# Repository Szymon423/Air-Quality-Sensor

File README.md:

<div align="center">

# Air Quality Sensor

**A compact, open-hardware indoor air quality monitor built around the ESP32-S3.**
Measures CO₂, temperature, humidity and pressure, and shows the room's air quality on a ring of RGB LEDs.

</div>

---

## Features

- **True CO₂ measurement.** Sensirion **SCD41** photoacoustic NDIR sensor, not an estimated eCO₂ value.
- **Temperature & humidity.** Sensirion **SHT4x**, placed on a thermally isolated PCB island (milled slot) to keep it away from heat from the MCU and regulator.
- **Barometric pressure.** Goertek **SPA06-003**.
- **Wi-Fi + Bluetooth LE.** **ESP32-S3-WROOM-1U** with an external antenna connector (U.FL).
- **16× WS2812 LED ring** on the bottom side, shining through a translucent diffuser. The 5 V data line goes through a 74AHCT1G125 level shifter.
- **USB-C power** with ESD protection (USBLC6-2) and fuses, plus a TPS54302 buck regulator for the 3.3 V rail.
- **Expansion port.** JST-PH 4-pin connector with 3.3 V, GND and two free GPIOs.
- **Debug UART header** and test points on every important net.
- **Round Ø70 mm PCB** in a 3D-printable enclosure with angled ventilation slots.

## Gallery

<table>
  <tr>
    <td align="center"><br><sub>USB-C side</sub></td>
    <td align="center"><br><sub>Bottom with LED diffuser</sub></td>
  </tr>
</table>

### PCB

<table>
  <tr>
    <td align="center" width="50%"><br><sub>Top side</sub></td>
    <td align="center" width="50%"><br><sub>Bottom side – LED ring</sub></td>
  </tr>
</table>

📄 **[Schematic (PDF)](docs/schematic.pdf)**

## Hardware overview

| Block | Part | Notes |
|---|---|---|
| MCU | ESP32-S3-WROOM-1U | Wi-Fi 4 / BLE 5, external antenna |
| CO₂ | Sensirion SCD41 | 400–5000 ppm, I²C |
| Temperature / RH | Sensirion SHT4x | I²C, thermally isolated |
| Pressure | Goertek SPA06-003 | I²C |
| Indicator | 16× WS2812C-2020 | Driven through 74AHCT1G125 level shifter |
| Power | USB-C → TPS54302 buck → 3.3 V | USBLC6-2 ESD protection, PTC fuses |
| PCB | Ø70 mm, round | Designed for JLCPCB assembly (LCSC part numbers in BOM) |

```
 USB-C ──► ESD + fuse ──► TPS54302 ──► 3.3 V ─┬─► ESP32-S3 ──I²C──┬─► SCD41  (CO₂)
   │                                          │       │           ├─► SHT4x  (T / RH)
   └──────────── 5 V ─────────────────────────┼───────┼──────┐    └─► SPA06  (pressure)
                                              │       │      ▼
                                              │       └──► 74AHCT1G125 ──► 16× WS2812 ring
                                              └─► JST-PH expansion (2× GPIO)
```

## Repository structure

```
.
├── 01_Hardware/
│   ├── 02_KiCad/
│   │   ├── air-quality-sensor/    # KiCad project (schematic + PCB)
│   │   │   └── production/        # Gerbers, BOM, pick & place (JLCPCB)
│   │   └── lib/                   # Custom symbols, footprints, 3D models
│   └── 03_3D_Model/
│       ├── 3D-Printing/           # Enclosure STL / 3MF files
│       └── test.blend             # Blender scene used for the renders
├── 02_Software/                   # Firmware (coming soon)
└── docs/                          # Images and schematic PDF for this README
```

## Roadmap

- [x] Schematic
- [x] PCB layout v0.1 (Ø70 mm)
- [x] Enclosure design & renders
- [ ] Order and assemble the first prototype
- [ ] Hardware bring-up & validation
- [ ] Firmware: sensor readout, LED air-quality indication
- [ ] Home Assistant integration (ESPHome / MQTT)
- [ ] Hardware v1.0 release

## Building one

> [!WARNING]
> This project is **work in progress**. Hardware v0.1 has not been manufactured and tested yet, so order boards at your own risk.

1. Open `01_Hardware/02_KiCad/air-quality-sensor/air-quality-sensor.kicad_pro` in **KiCad 10**.
2. The fabrication files (Gerbers, BOM, CPL) for JLCPCB are in `production/`.
3. Print the enclosure from `01_Hardware/03_3D_Model/3D-Printing/`.

## License

**Hardware** (schematics, PCB, enclosure, renders): [**CC BY-NC-SA 4.0**](LICENSE).
You may build, study and modify this design for **non-commercial** purposes, as long as you credit the author and share your changes under the same license.
**Selling boards, kits or devices based on this design is not allowed** without the author's written permission.

**Firmware** (`02_Software/`): [**GPL-3.0**](02_Software/LICENSE).

For commercial licensing, please get in touch.

---

<div align="center">
<sub>Designed by <b>Szymon Wąchała</b> · 2026</sub>
</div>

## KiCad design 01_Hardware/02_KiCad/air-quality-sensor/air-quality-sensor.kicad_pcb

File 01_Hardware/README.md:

# Hardware | Air Quality Sensor

| Folder | Contents |
|---|---|
| [`02_KiCad/air-quality-sensor`](02_KiCad/air-quality-sensor) | KiCad 10 project: schematic sheets (`mcu`, `sensors`, `led-ring`, `power-section`) and PCB |
| [`02_KiCad/air-quality-sensor/production`](02_KiCad/air-quality-sensor/production) | JLCPCB fabrication output: Gerbers, BOM, pick & place |
| [`02_KiCad/lib`](02_KiCad/lib) | Project-specific libraries and 3D models |
| [`03_3D_Model/3D-Printing`](03_3D_Model/3D-Printing) | Enclosure parts for 3D printing |

A PDF of the schematic is in [`docs/schematic.pdf`](../docs/schematic.pdf).

Licensed under [CC BY-NC-SA 4.0](../LICENSE).

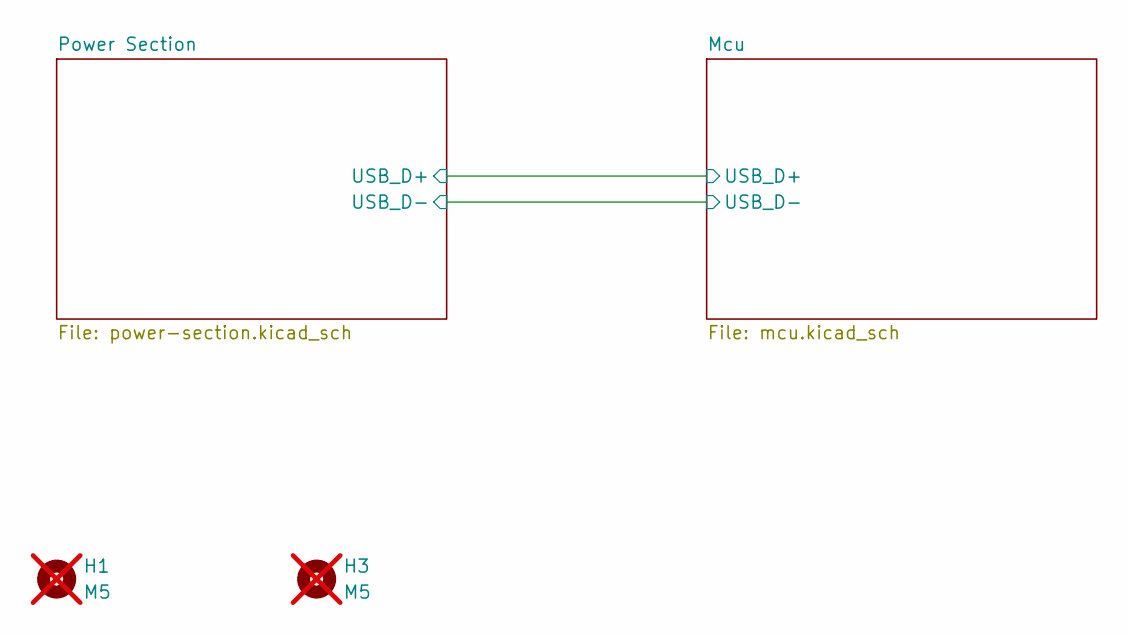
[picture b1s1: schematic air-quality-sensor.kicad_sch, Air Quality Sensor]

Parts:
H1, H3: M5; MountingHole_5mm; not fitted

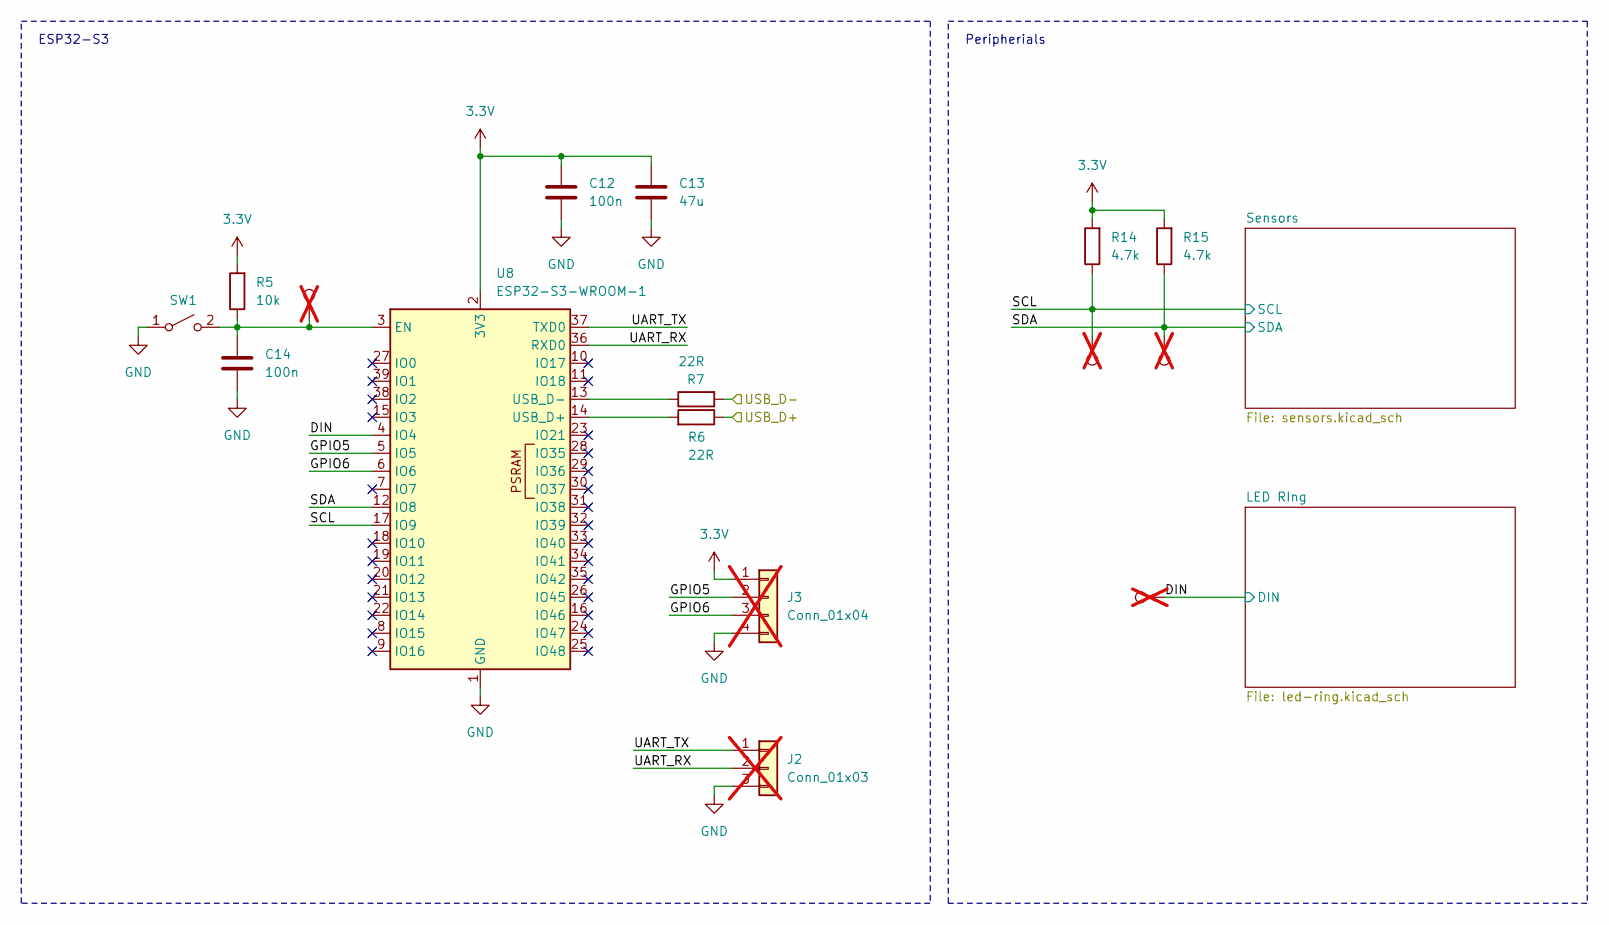
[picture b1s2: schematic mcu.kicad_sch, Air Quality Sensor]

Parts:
C12, C14: 100n; C_0603_1608Metric; LCSC C14663
C13: 47u; C_1206_3216Metric; LCSC C96123
J2: Conn_01x03; PinHeader_1x03_P2.54mm_Vertical; not fitted
J3: Conn_01x04; JST_PH_B4B-PH-K_1x04_P2.00mm_Vertical; not fitted
R5: 10k; R_0603_1608Metric; LCSC C22369937
R6, R7: 22R; R_0603_1608Metric; LCSC C23345
R14, R15: 4.7k; R_0603_1608Metric; LCSC C23162
SW1: SW_SPST; SW_Push_1P1T_NO_CK_KMR2; LCSC C72443
TP4, TP5, TP6, TP9: 3.3V; TestPoint_Pad_D1.0mm; not fitted
U8: ESP32-S3-WROOM-1; ESP32-S3-WROOM-1U; LCSC C2980297

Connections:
3.3V: C12.2, C13.1, J3.1, R5.2, R14.2, R15.2, U8.2 (3V3); also elsewhere on the board
/Mcu/DIN: TP9.1 (1_1), U8.4 (IO4); also elsewhere on the board
/Mcu/GPIO5: J3.2, U8.5 (IO5)
/Mcu/GPIO6: J3.3, U8.6 (IO6)
/Mcu/SCL: R14.1, TP5.1 (1_1), U8.17 (IO9); also elsewhere on the board
/Mcu/SDA: R15.1, TP4.1 (1_1), U8.12 (IO8); also elsewhere on the board
/Mcu/UART_RX: J2.2, U8.36 (RXD0)
/Mcu/UART_TX: J2.1, U8.37 (TXD0)
/Mcu/USB_D+: R6.1; also elsewhere on the board
/Mcu/USB_D-: R7.2; also elsewhere on the board
GND: C12.1, C13.2, C14.1, J2.3, J3.4, SW1.1 (A), U8.1 (GND), U8.40 (GND), U8.41 (GND); also elsewhere on the board
unnamed: C14.2, R5.1, SW1.2 (B), TP6.1 (1_1), U8.3 (EN)
unnamed: R6.2, U8.14 (USB_D+)
unnamed: R7.1, U8.13 (USB_D-)

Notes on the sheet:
ESP32-S3
Peripherials

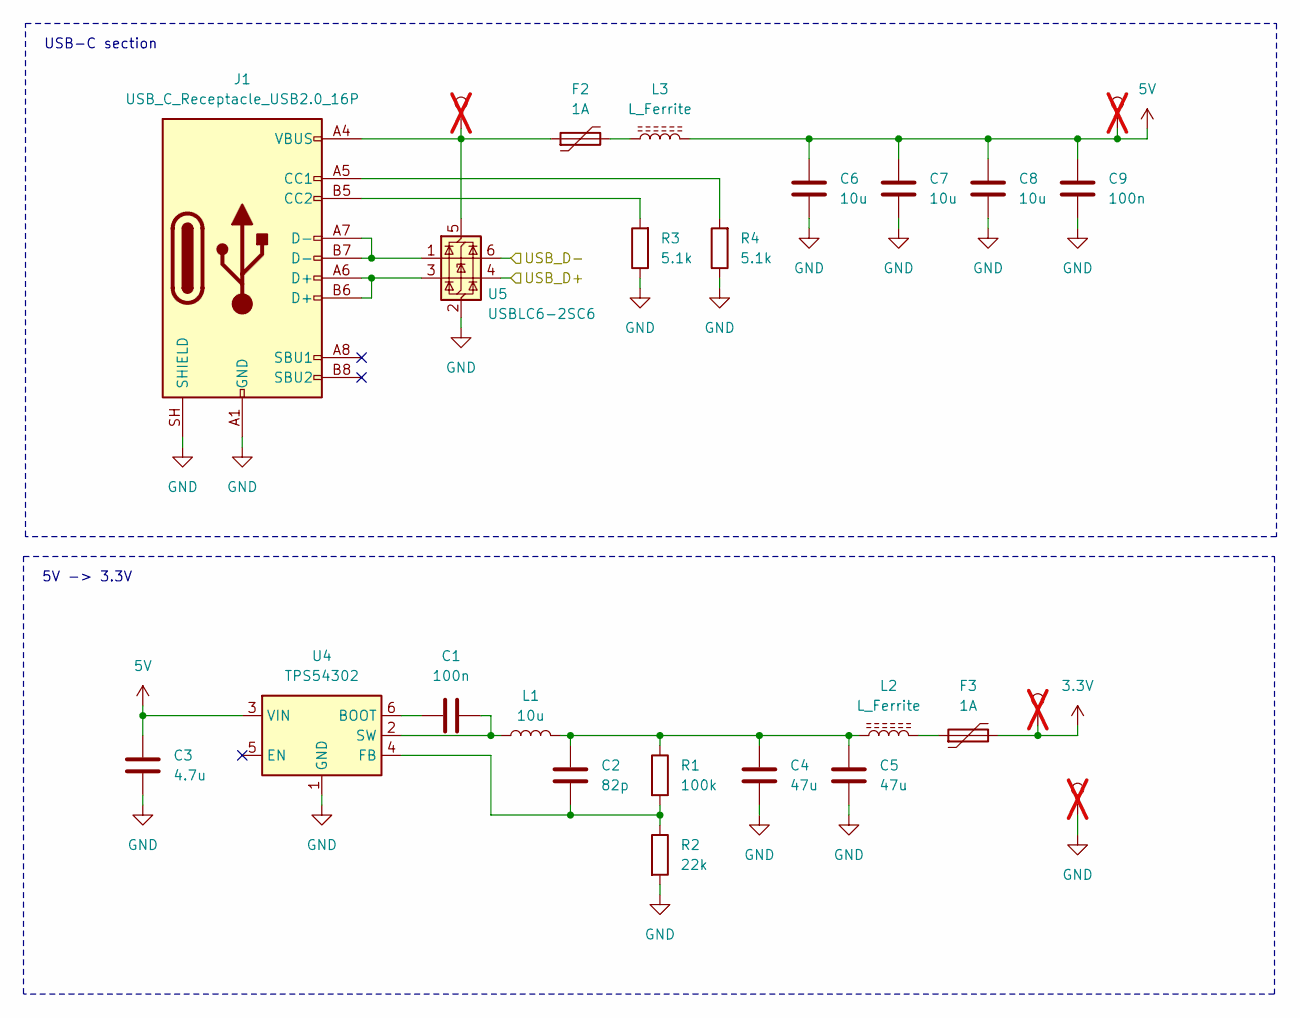
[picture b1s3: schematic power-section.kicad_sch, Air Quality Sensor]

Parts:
C1, C9: 100n; C_0603_1608Metric; LCSC C14663
C2: 82p; C_0603_1608Metric; LCSC C1683
C3: 4.7u; C_0805_2012Metric; LCSC C1779
C4, C5: 47u; C_1206_3216Metric; LCSC C96123
C6, C7, C8: 10u; C_1206_3216Metric; LCSC C13585
F2, F3: 1A; R_1206_3216Metric; LCSC C561579
J1: USB_C_Receptacle_USB2.0_16P; USB_C_Receptacle_GCT_USB4105-xx-A_16P_TopMnt_Horizontal; LCSC C3020560
L1: 10u; L_APV_ANR6045; LCSC C354632
L2, L3: L_Ferrite; L_0603_1608Metric; LCSC C14709
R1: 100k; R_0603_1608Metric; LCSC C25803
R2: 22k; R_0603_1608Metric; LCSC C31850
R3, R4: 5.1k; R_0603_1608Metric; LCSC C23186
TP1, TP2, TP3, TP10: 3.3V; TestPoint_Pad_D1.0mm; not fitted
U4: TPS54302; SOT-23-6; LCSC C129370
U5: USBLC6-2SC6; SOT-23-6; LCSC C558442

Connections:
3.3V: F3.2, TP1.1 (1_1); also elsewhere on the board
5V: C3.1, C6.1, C7.1, C8.1, C9.2, L3.2, TP2.1 (1_1), U4.3 (VIN); also elsewhere on the board
/Mcu/USB_D+: U5.4 (I/O2); also elsewhere on the board
/Mcu/USB_D-: U5.6 (I/O1); also elsewhere on the board
GND: C3.2, C4.2, C5.2, C6.2, C7.2, C8.2, C9.1, J1.A1 (GND), J1.A12 (GND), J1.B1 (GND), J1.B12 (GND), J1.SH (SHIELD), R2.2, R3.1, R4.1, TP10.1 (1_1), U4.1 (GND), U5.2 (GND); also elsewhere on the board
unnamed: C2.2, C4.1, C5.1, L1.2, L2.1, R1.1
unnamed: F2.2, L3.1
unnamed: F3.1, L2.2
unnamed: J1.A5 (CC1), R4.2
unnamed: J1.B5 (CC2), R3.2
unnamed: J1.A6 (D+), J1.B6 (D+), U5.3 (I/O2)
unnamed: J1.A7 (D-), J1.B7 (D-), U5.1 (I/O1)
unnamed: C1.1, U4.6 (BOOT)
unnamed: C2.1, R1.2, R2.1, U4.4 (FB)
unnamed: C1.2, L1.1, U4.2 (SW)
unnamed: F2.1, J1.A4 (VBUS), J1.A9 (VBUS), J1.B4 (VBUS), J1.B9 (VBUS), TP3.1 (1_1), U5.5 (VBUS)

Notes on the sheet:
5V -> 3.3V
USB-C section

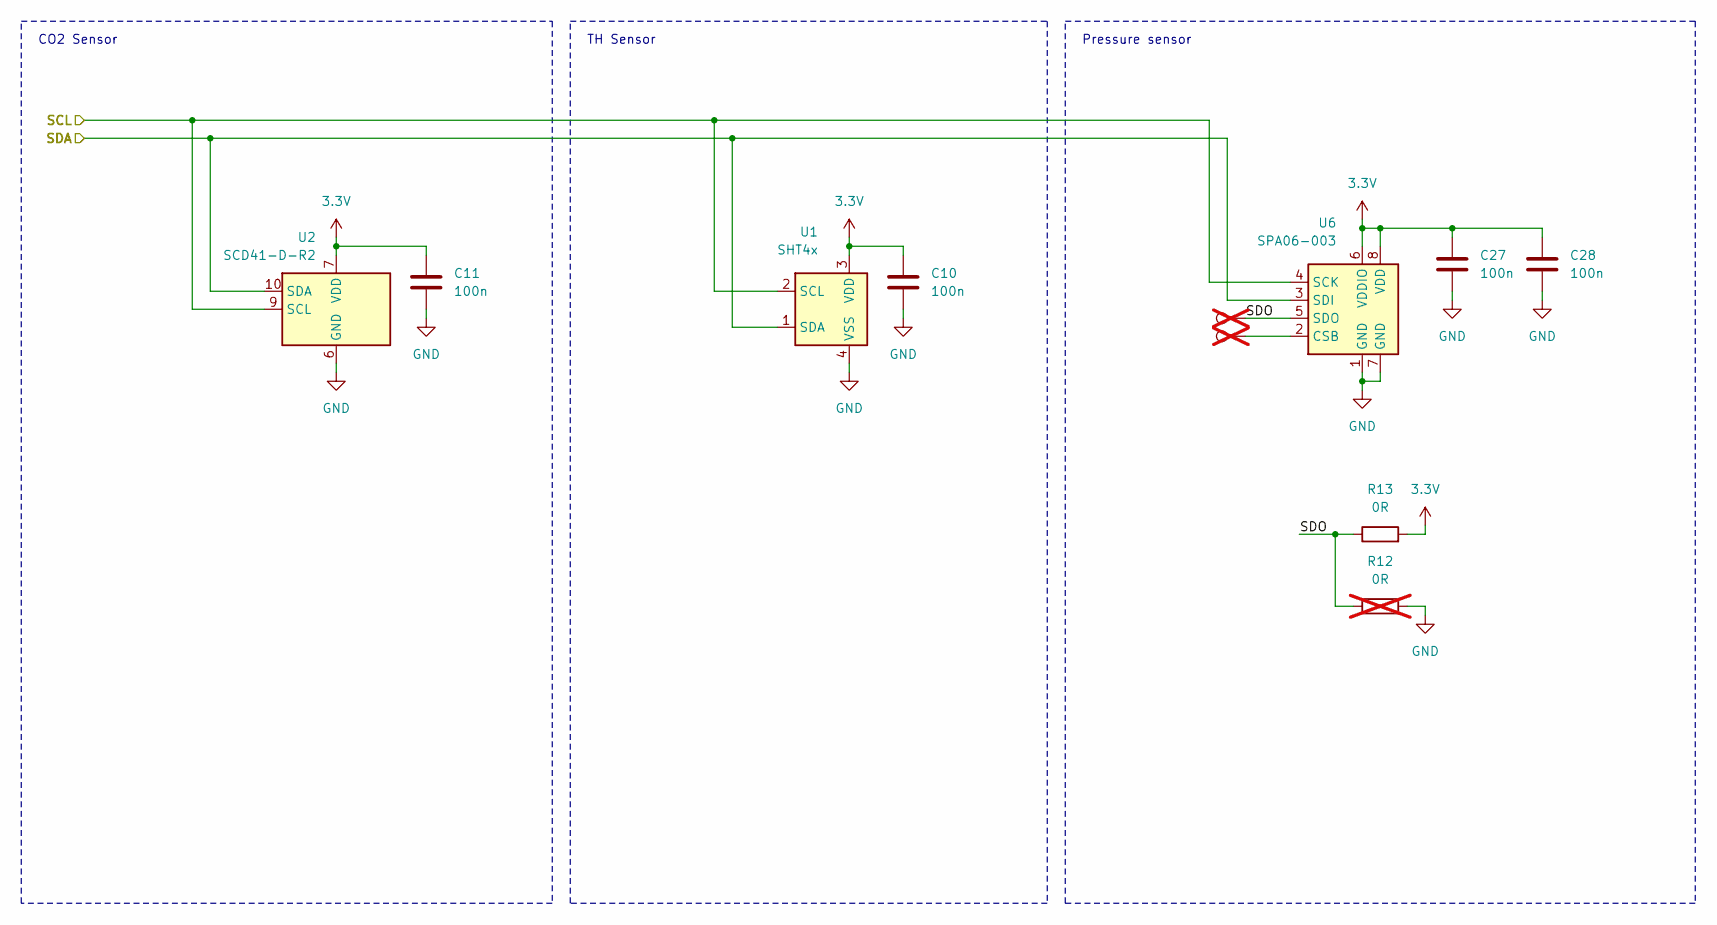
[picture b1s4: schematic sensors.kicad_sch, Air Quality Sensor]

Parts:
C10, C11, C27, C28: 100n; C_0603_1608Metric; LCSC C14663
R12: 0R; R_0603_1608Metric; LCSC C21189; not fitted
R13: 0R; R_0603_1608Metric; LCSC C21189
TP7, TP8: 3.3V; TestPoint_Pad_D1.0mm; not fitted
U1: SHT4x; Sensirion_DFN-4_1.5x1.5mm_P0.8mm_SHT4x_NoCentralPad; LCSC C7461862
U2: SCD41-D-R2; Sensirion_SCD4x-1EP_10.1x10.1mm_P1.25mm_EP4.8x4.8mm; LCSC C3037696
U6: SPA06-003; Bosch_LGA-8_2x2.5mm_P0.65mm_ClockwisePinNumbering; LCSC C30589048

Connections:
3.3V: C10.2, C11.2, C27.1, C28.1, R13.2, U1.3 (VDD), U2.7 (VDD), U2.19 (VDD), U6.6 (VDDIO), U6.8 (VDD); also elsewhere on the board
/Mcu/SCL: U1.2 (SCL), U2.9 (SCL), U6.4 (SCK); also elsewhere on the board
/Mcu/SDA: U1.1 (SDA), U2.10 (SDA), U6.3 (SDI); also elsewhere on the board
/Mcu/Sensors/SDO: R12.1, R13.1, TP7.1 (1_1), U6.5 (SDO)
GND: C10.1, C11.1, C27.2, C28.2, R12.2, U1.4 (VSS), U2.6 (GND), U2.20 (GND), U2.21 (GND), U6.1 (GND), U6.7 (GND); also elsewhere on the board
unnamed: TP8.1 (1_1), U6.2 (CSB)

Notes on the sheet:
TH Sensor
CO2 Sensor
Pressure sensor

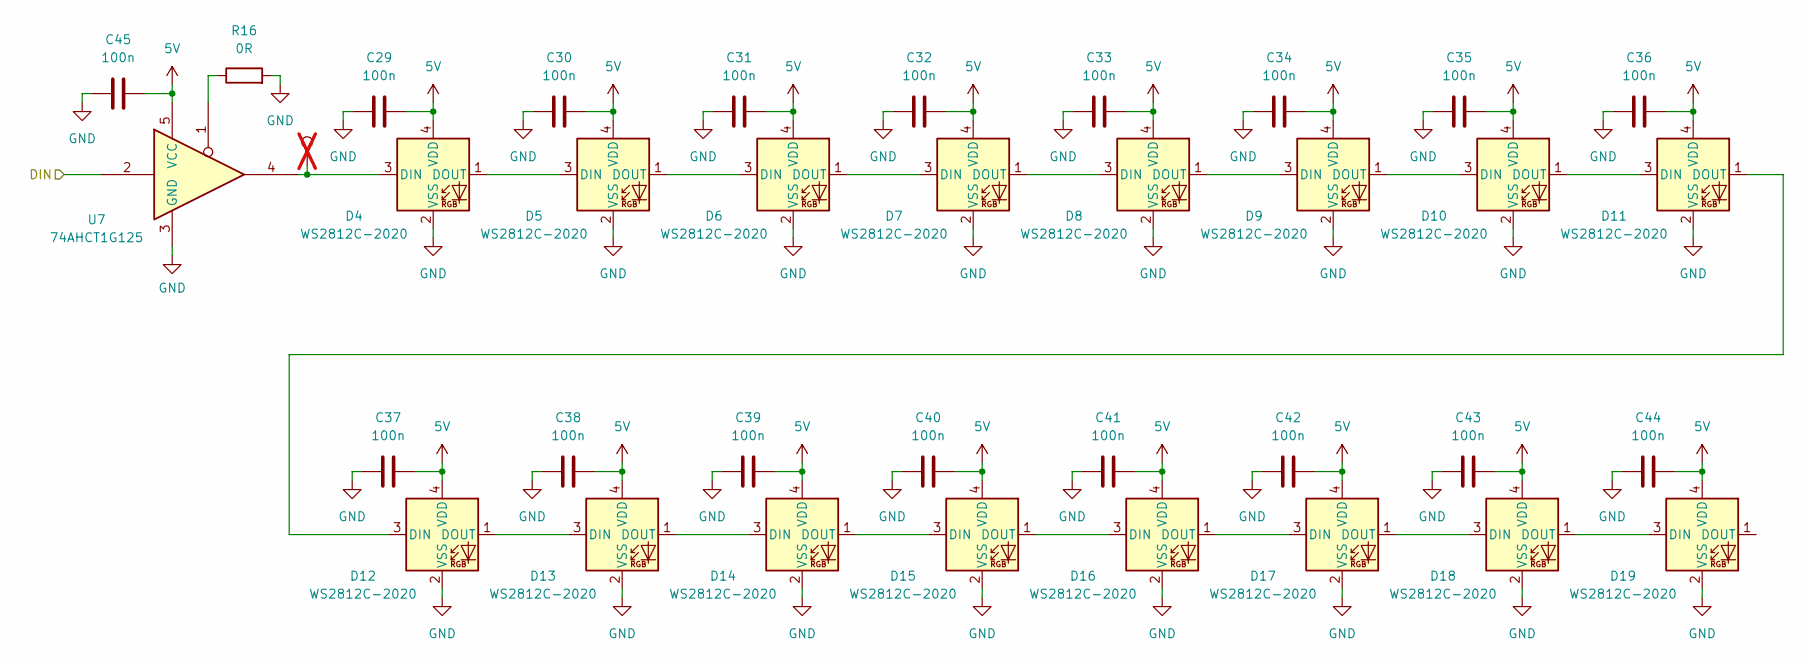
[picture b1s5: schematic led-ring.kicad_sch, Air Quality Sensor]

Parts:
C29, C30, C31, C32, C33, C34, C35, C36, C37, C38, C39, C40, C41, C42, C43, C44, C45: 100n; C_0603_1608Metric; LCSC C14663
D4, D5, D6, D7, D8, D9, D10, D11, D12, D13, D14, D15, D16, D17, D18, D19: WS2812C-2020; LED_WS2812B-2020_PLCC4_2.0x2.0mm; LCSC C2976072
R16: 0R; R_0603_1608Metric; LCSC C21189
TP19: 3.3V; TestPoint_Pad_D1.0mm; not fitted
U7: 74AHCT1G125; SOT-23-5; LCSC C52140417

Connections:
5V: C29.1, C30.1, C31.1, C32.1, C33.1, C34.1, C35.1, C36.1, C37.1, C38.1, C39.1, C40.1, C41.1, C42.1, C43.1, C44.1, C45.1, D4.4 (VDD), D5.4 (VDD), D6.4 (VDD), D7.4 (VDD), D8.4 (VDD), D9.4 (VDD), D10.4 (VDD), D11.4 (VDD), D12.4 (VDD), D13.4 (VDD), D14.4 (VDD), D15.4 (VDD), D16.4 (VDD), D17.4 (VDD), D18.4 (VDD), D19.4 (VDD), U7.5 (VCC); also elsewhere on the board
/Mcu/DIN: U7.2; also elsewhere on the board
GND: C29.2, C30.2, C31.2, C32.2, C33.2, C34.2, C35.2, C36.2, C37.2, C38.2, C39.2, C40.2, C41.2, C42.2, C43.2, C44.2, C45.2, D4.2 (VSS), D5.2 (VSS), D6.2 (VSS), D7.2 (VSS), D8.2 (VSS), D9.2 (VSS), D10.2 (VSS), D11.2 (VSS), D12.2 (VSS), D13.2 (VSS), D14.2 (VSS), D15.2 (VSS), D16.2 (VSS), D17.2 (VSS), D18.2 (VSS), D19.2 (VSS), R16.2, U7.3 (GND); also elsewhere on the board
unnamed: D4.3 (DIN), TP19.1 (1_1), U7.4
unnamed: D4.1 (DOUT), D5.3 (DIN)
unnamed: D5.1 (DOUT), D6.3 (DIN)
unnamed: D6.1 (DOUT), D7.3 (DIN)
unnamed: D7.1 (DOUT), D8.3 (DIN)
unnamed: D8.1 (DOUT), D9.3 (DIN)
unnamed: D9.1 (DOUT), D10.3 (DIN)
unnamed: D10.1 (DOUT), D11.3 (DIN)
unnamed: D11.1 (DOUT), D12.3 (DIN)
unnamed: D12.1 (DOUT), D13.3 (DIN)
unnamed: D13.1 (DOUT), D14.3 (DIN)
unnamed: D14.1 (DOUT), D15.3 (DIN)
unnamed: D15.1 (DOUT), D16.3 (DIN)
unnamed: D16.1 (DOUT), D17.3 (DIN)
unnamed: D17.1 (DOUT), D18.3 (DIN)
unnamed: D18.1 (DOUT), D19.3 (DIN)
unnamed: R16.1, U7.1

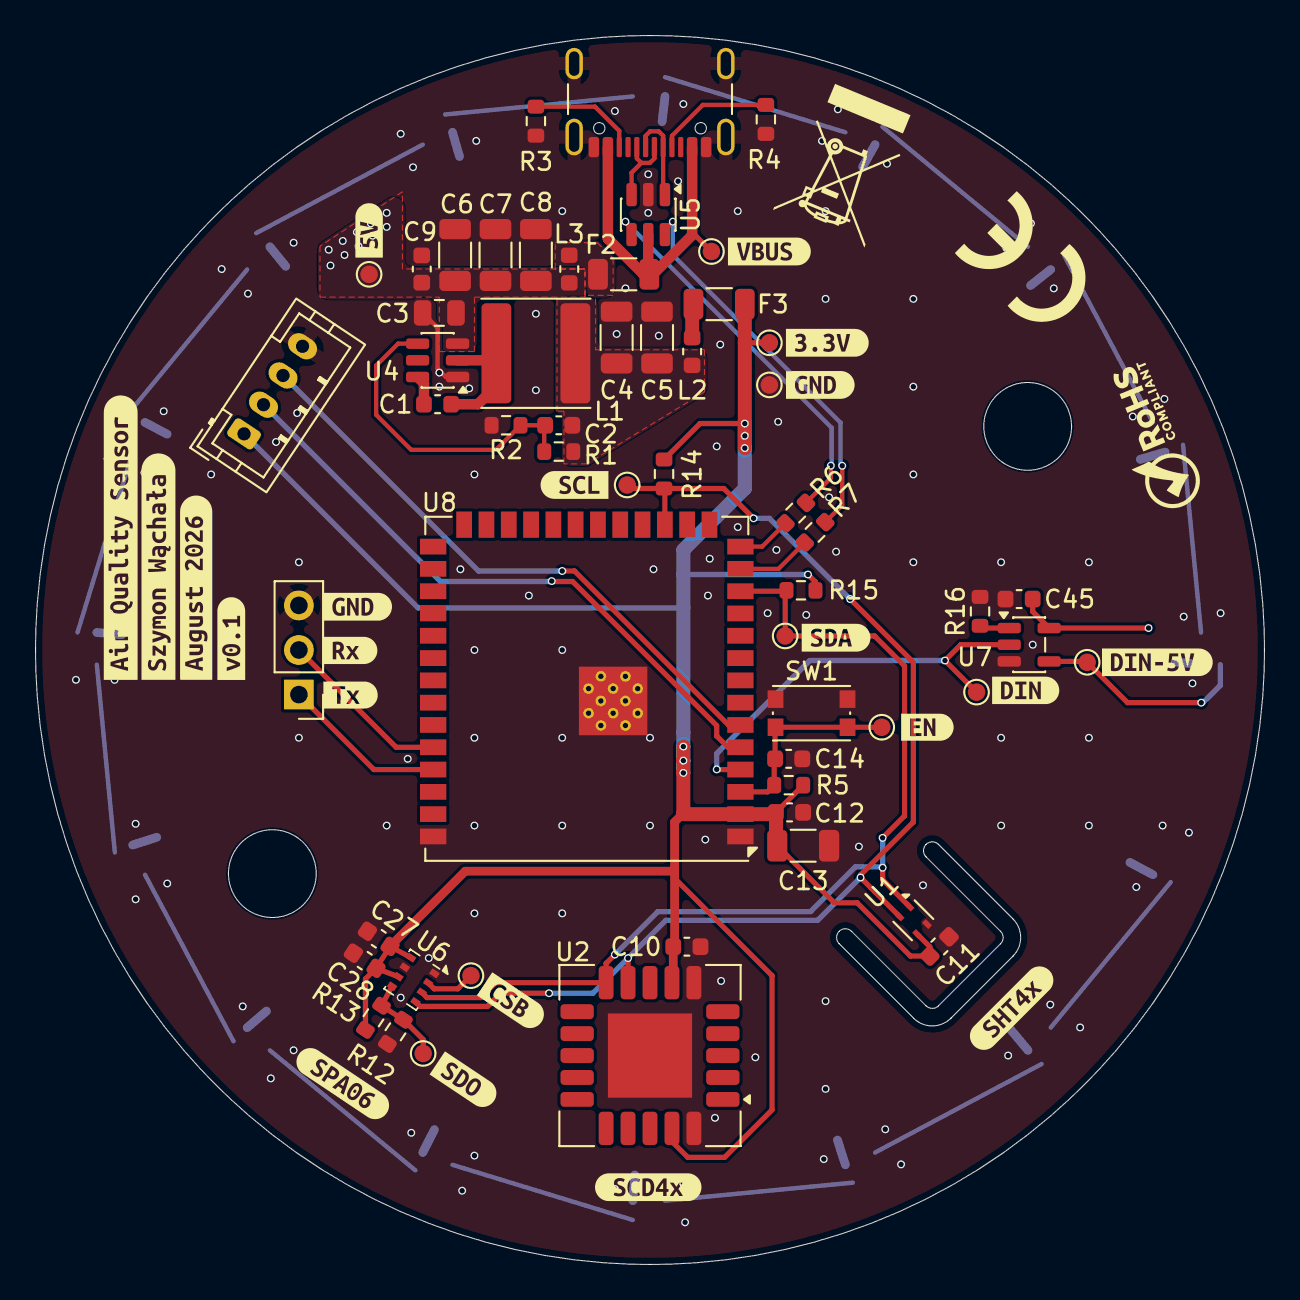
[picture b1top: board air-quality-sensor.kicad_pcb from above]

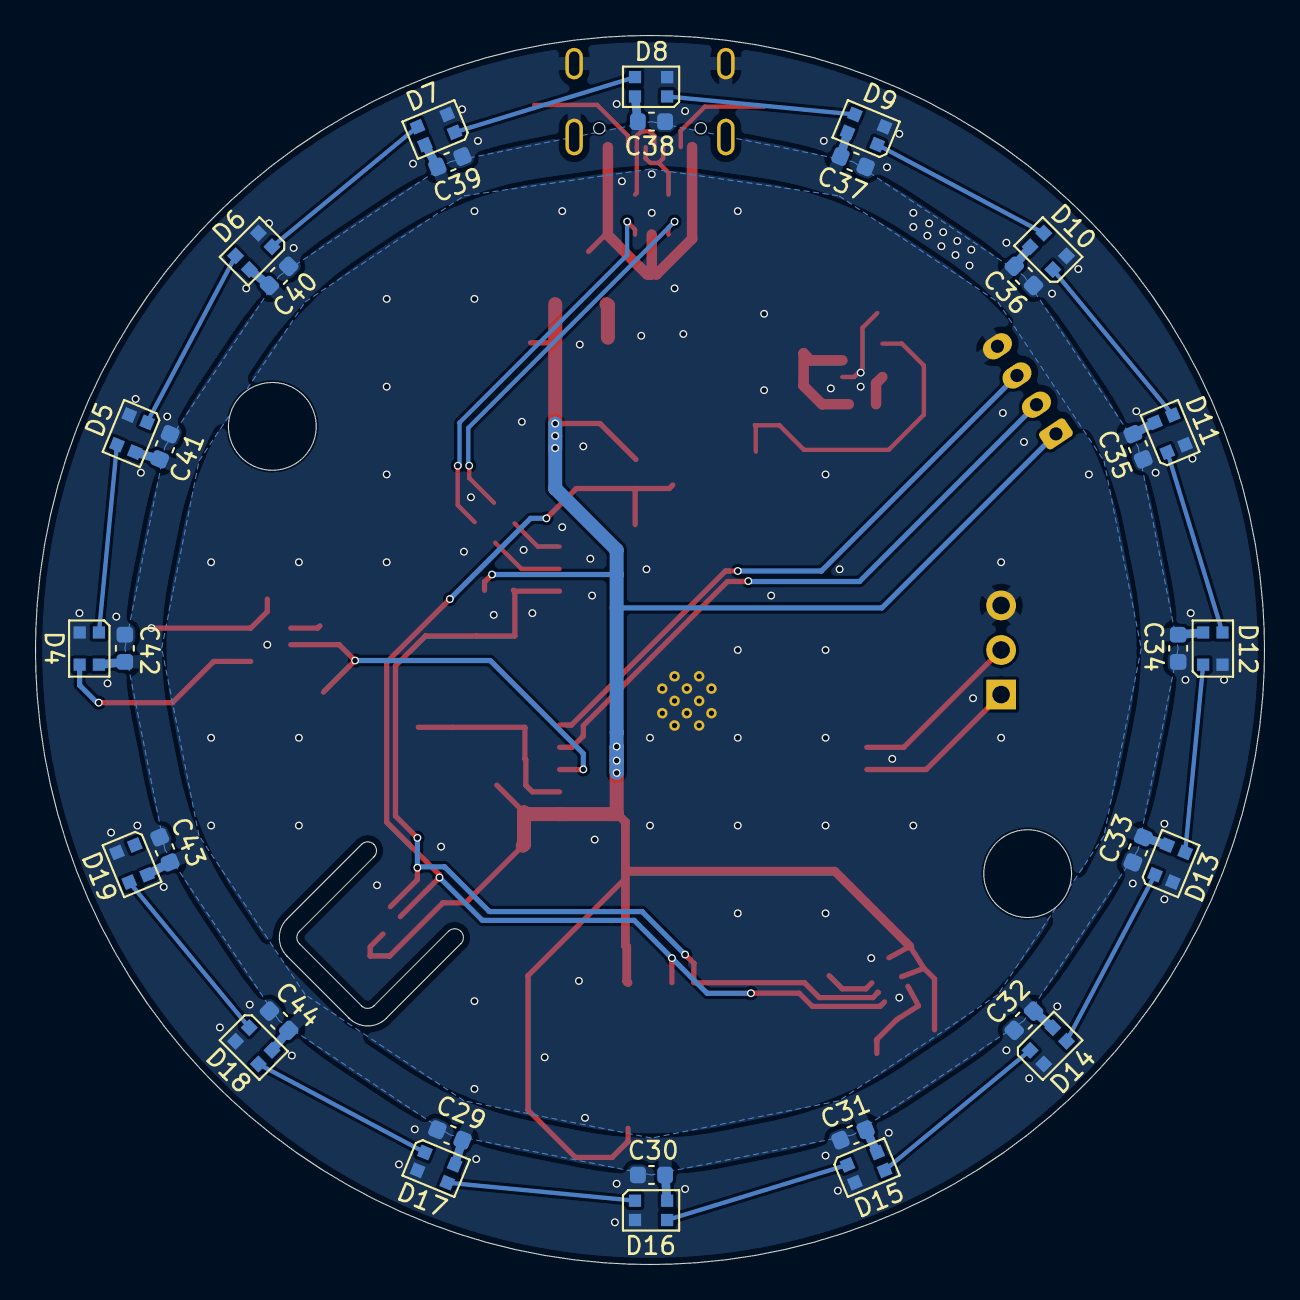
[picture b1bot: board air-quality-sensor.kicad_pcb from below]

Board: 2 copper layers, 70.0 x 70.0 mm, 111 parts (32 on the bottom side), 45 nets.

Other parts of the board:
kibuzzard-6A7E4C1B: G***; kibuzzard-6A7E4C1B
kibuzzard-6A7E4C16: G***; kibuzzard-6A7E4C16
kibuzzard-6A7E4C25: G***; kibuzzard-6A7E4C25
kibuzzard-6A7E4C33: G***; kibuzzard-6A7E4C33
kibuzzard-6A7E44B1: G***; kibuzzard-6A7E44B1
kibuzzard-6A7E44DD: G***; kibuzzard-6A7E44DD
kibuzzard-6A7E44FE: G***; kibuzzard-6A7E44FE
kibuzzard-6A7E45B3: G***; kibuzzard-6A7E45B3
kibuzzard-6A7E45BF: G***; kibuzzard-6A7E45BF
kibuzzard-6A7E45D0: G***; kibuzzard-6A7E45D0
kibuzzard-6A7E47FA: G***; kibuzzard-6A7E47FA
kibuzzard-6A7E446E: G***; kibuzzard-6A7E446E
kibuzzard-6A7E450C: G***; kibuzzard-6A7E450C
kibuzzard-6A7E453D: G***; kibuzzard-6A7E453D
kibuzzard-6A7E4485: G***; kibuzzard-6A7E4485
kibuzzard-6A7E4494: G***; kibuzzard-6A7E4494
kibuzzard-6A7E4579: G***; kibuzzard-6A7E4579
kibuzzard-6A7E4598: G***; kibuzzard-6A7E4598
kibuzzard-6A80ED83: G***; kibuzzard-6A80ED83
kibuzzard-6A80EDA5: G***; kibuzzard-6A80EDA5
kibuzzard-6A80EDE6: G***; kibuzzard-6A80EDE6

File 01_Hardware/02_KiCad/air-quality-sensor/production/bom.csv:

Designator,Footprint,Quantity,Value,LCSC Part #
"C1, C10, C11, C12, C14, C27, C28, C29, C30, C31, C32, C33, C34, C35, C36, C37, C38, C39, C40, C41, C42, C43, C44, C45, C9",0603,25,100n,C14663
"C13, C4, C5",1206,3,47u,C96123
C2,0603,1,82p,C1683
C3,0805,1,4.7u,C1779
"C6, C7, C8",1206,3,10u,C13585
"D10, D11, D12, D13, D14, D15, D16, D17, D18, D19, D4, D5, D6, D7, D8, D9",LED_WS2812B-2020_PLCC4_2.0x2.0mm,16,WS2812C-2020,C2976072
"F2, F3",1206,2,1A,C561579
J1,USB_C_Receptacle_GCT_USB4105-xx-A_16P_TopMnt_Horizontal,1,USB_C_Receptacle_USB2.0_16P,C3020560
L1,L_APV_ANR6045,1,10u,C354632
"L2, L3",0603,2,L_Ferrite,C14709
R1,0603,1,100k,C25803
R13,0603,1,0R,C21189
"R14, R15",0603,2,4.7k,C23162
R16,0603,1,0R,
R2,0603,1,22k,C31850
"R3, R4",0603,2,5.1k,C23186
R5,0603,1,10k,C22369937
"R6, R7",0603,2,22R,C23345
SW1,SW_Push_1P1T_NO_CK_KMR2,1,SW_SPST,C72443
U1,Sensirion_DFN-4_1.5x1.5mm_P0.8mm_SHT4x_NoCentralPad,1,SHT4x,C7461862
U2,Sensirion_SCD4x-1EP_10.1x10.1mm_P1.25mm_EP4.8x4.8mm,1,SCD41-D-R2,C3037696
U4,SOT-23-6,1,TPS54302,C129370
U5,SOT-23-6,1,USBLC6-2SC6,C558442
U6,Bosch_LGA-8_2x2.5mm_P0.65mm_ClockwisePinNumbering,1,SPA06-003,C30589048
U7,SOT-23-5,1,74AHCT1G125,C52140417
U8,ESP32-S3-WROOM-1U,1,ESP32-S3-WROOM-1,C2980297

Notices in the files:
README.md:
License: CC BY-NC-SA 4.0
